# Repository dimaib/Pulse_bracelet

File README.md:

# Oxemetry and pulsometry
## Description
This system allows you to distribute people between warehouse equipment and give permission to control certain types of machines. It also allows you to take into account the working hours of employees and conduct convenient analytics according to these hours.
## System Composition
- Wrist bracelet
	>The printed circuit board and circuit diagram of the device are created in [KiCad](https://www.kicad.org) 
	Firmware created in Keil uVision for ARM in C languages
- Server that receives data from devices and adds this data to the database
	>The server part was created in Visual Studio C ++, as a console application
	MySQL was used as the database. And MySQL Workbench for administration

## Main view PCB

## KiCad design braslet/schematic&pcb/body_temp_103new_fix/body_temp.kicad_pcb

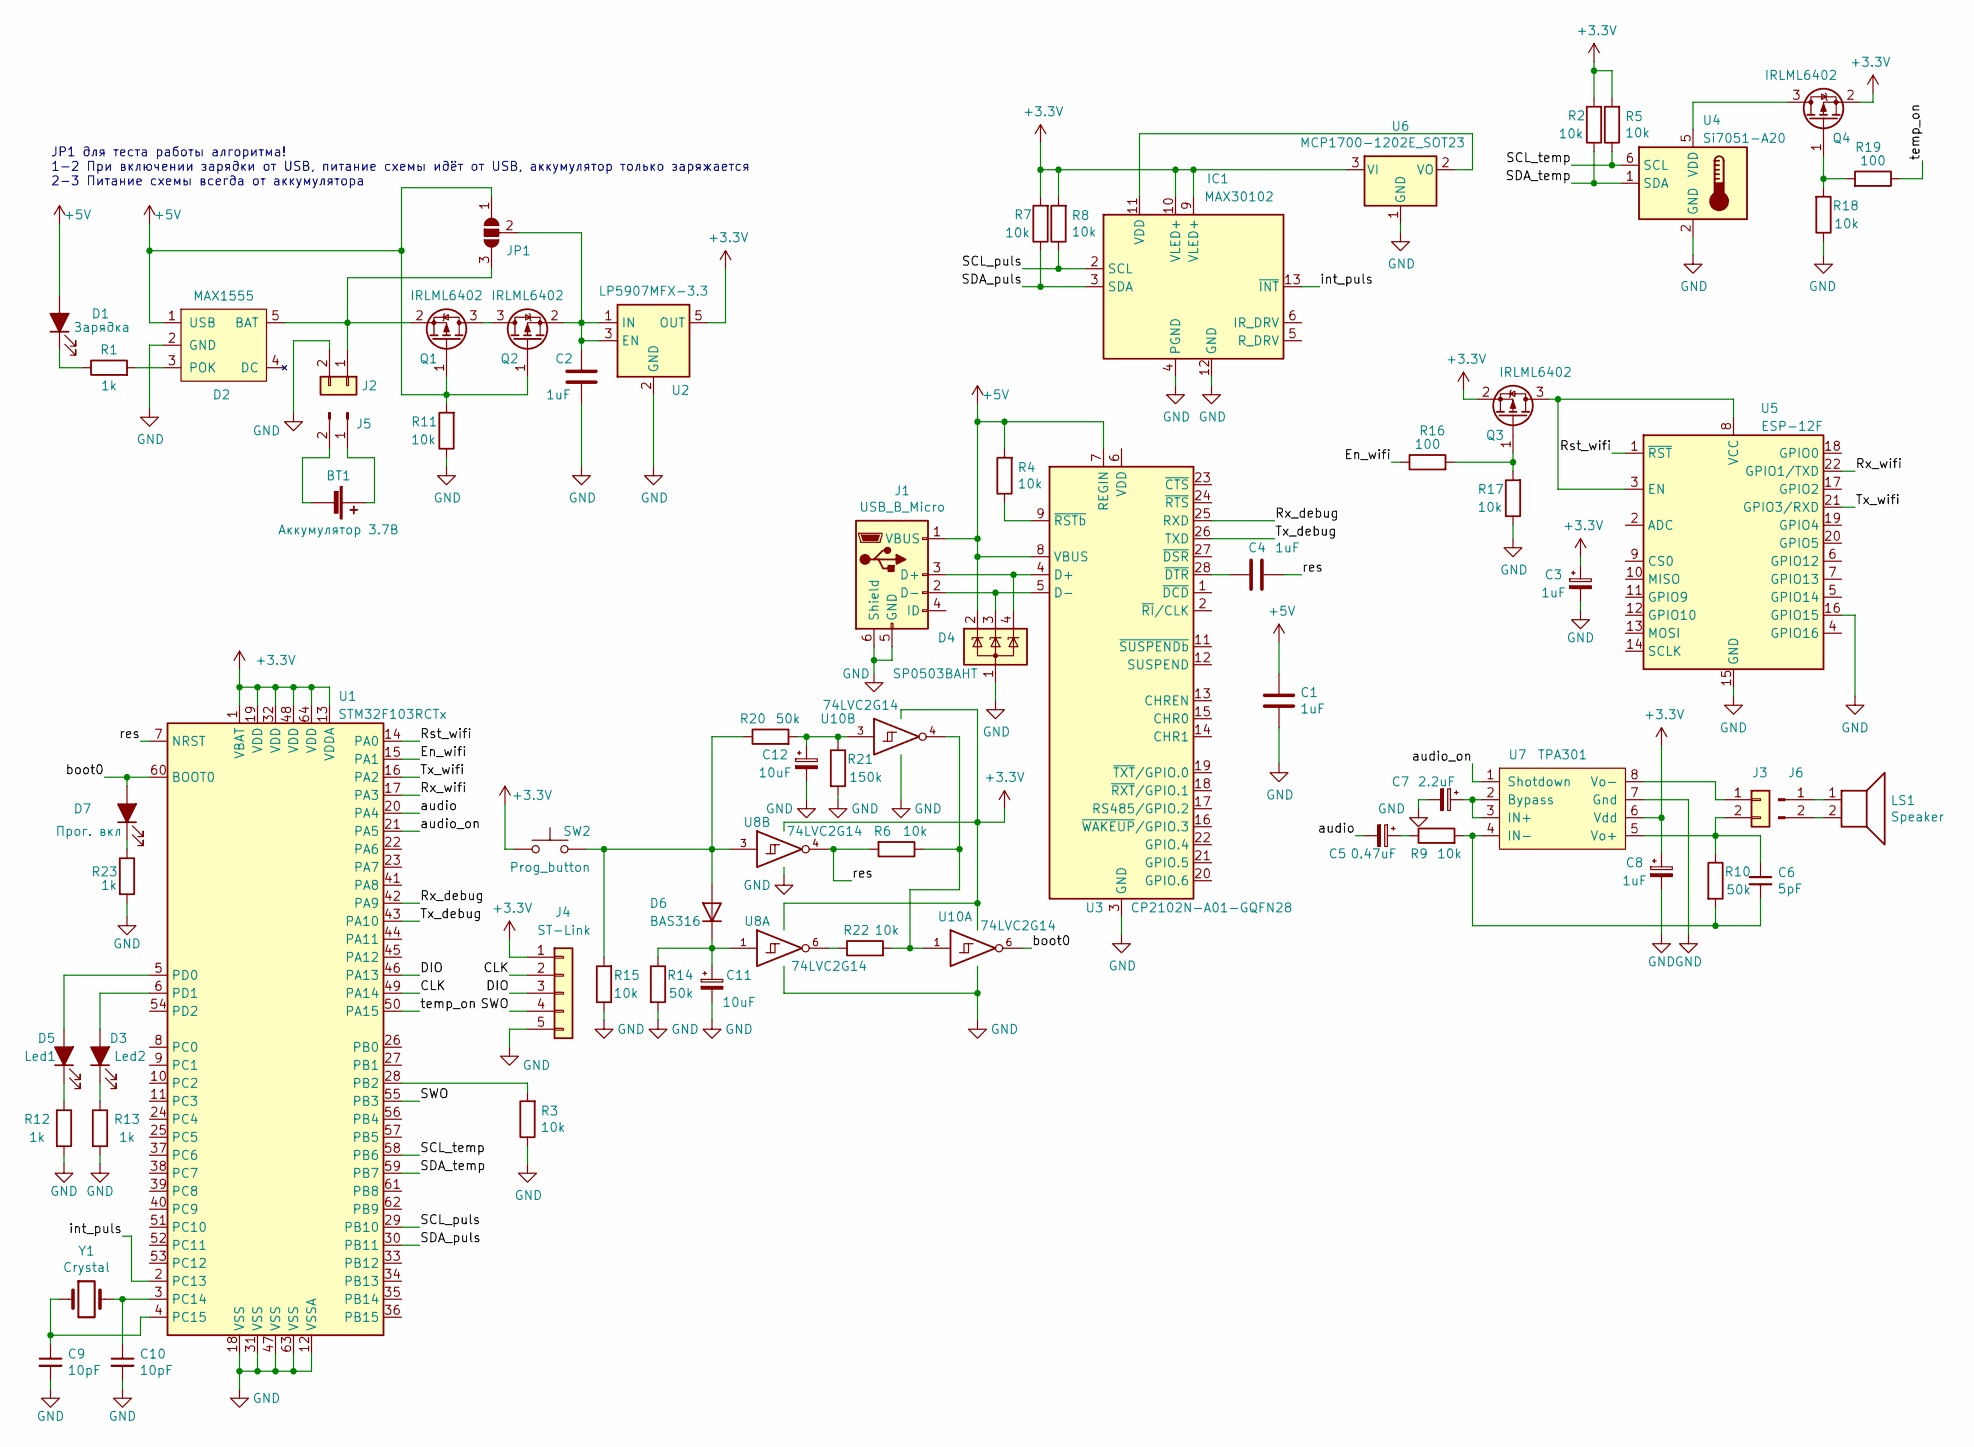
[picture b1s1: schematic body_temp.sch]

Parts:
BT1: Аккумулятор 3.7В
C1, C2, C4: 1uF; C_0603_1608Metric
C3, C8: 1uF; CP_EIA-3216-18_Kemet-A
C5: 0.47uF; CP_EIA-3216-18_Kemet-A
C6: 5pF; C_0603_1608Metric
C7: 2.2uF; CP_EIA-3216-18_Kemet-A
C9, C10: 10pF; C_0603_1608Metric
C11, C12: 10uF; CP_EIA-3216-18_Kemet-A
D1: Зарядка; LED_0603_1608Metric
D2: MAX1555; SOT-23-5
D3: Led2; LED_0603_1608Metric
D4: SP0503BAHT; SOT-143
D5: Led1; LED_0603_1608Metric
D6: BAS316; D_SOD-323
D7: Прог. вкл; LED_0603_1608Metric
IC1: MAX30102; Maxim_OLGA-14_3.3x5.6mm_P0.8mm
J1: USB_B_Micro; USB_Micro-B_Molex-105017-0001
J2: Аккумулятор на плату; ZH_Conn_02x01
J3: Динамик на плату; ZH_Conn_02x01
J4: ST-Link; ds1066-05m_2.0mm
J5: Аккумулятор на кабель
J6: Динамик на кабель
JP1: SolderJumper_3_Open; SolderJumper-3_P1.3mm_Open_RoundedPad1.0x1.5mm
LS1: Speaker
Q1, Q2, Q3, Q4: IRLML6402; SOT-23
R1, R12, R13, R23: 1k; R_0603_1608Metric
R2, R3, R4, R5, R6, R7, R8, R9, R11, R15, R17, R18, R22: 10k; R_0603_1608Metric
R10, R14, R20: 50k; R_0603_1608Metric
R16, R19: 100; R_0603_1608Metric
R21: 150k; R_0603_1608Metric
SW2: Prog_button; SW_SPST_EVQP7C
U1: STM32F103RCTx; LQFP-64_10x10mm_P0.5mm
U2: LP5907MFX-3.3; SOT-23-5
U3: CP2102N-A01-GQFN28; QFN-28-1EP_5x5mm_P0.5mm_EP3.35x3.35mm
U4: Si7051-A20; DFN-6-1EP_3x3mm_P1mm_EP1.5x2.4mm
U5: ESP-12F; ESP-12E
U6: MCP1700-1202E_SOT23; SOT-23
U7: TPA301; MSOP-8-1EP_3x3mm_P0.65mm_EP1.95x2.15mm
U8, U10: 74LVC2G14; SOT-23-6
Y1: Crystal; Crystal_SMD_G8-2Pin_3.2x1.5mm

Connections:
+3V3: C3.1, C8.1, IC1.9 (VLED+), IC1.10 (VLED+), J4.1, Q3.2 (S), Q4.2 (S), R2.2, R5.2, R7.2, R8.2, SW2.1, U1.1 (VBAT), U1.13 (VDDA), U1.19 (VDD), U1.32 (VDD), U1.48 (VDD), U1.64 (VDD), U2.5 (OUT), U6.3 (VI), U7.6 (Vdd), U8.5 (VCC), U10.5 (VCC)
+5V: C1.1, D1.2 (A), D2.1 (USB), D4.2 (K), J1.1 (VBUS), JP1.1 (A), Q1.1 (G), Q2.1 (G), R4.2, R11.2, U3.7 (REGIN), U3.8 (VBUS)
/CLK: J4.2, U1.49 (PA14)
/DIO: J4.3, U1.46 (PA13)
/En_wifi: R16.1, U1.15 (PA1)
/Rst_wifi: U1.14 (PA0), U5.1 (~RST)
/Rx_debug: U1.42 (PA9), U3.25 (RXD)
/Rx_wifi: U1.17 (PA3), U5.22 (GPIO1/TXD)
/SCL_puls: IC1.2 (SCL), R8.1, U1.29 (PB10)
/SCL_temp: R5.1, U1.58 (PB6), U4.6 (SCL)
/SDA_puls: IC1.3 (SDA), R7.1, U1.30 (PB11)
/SDA_temp: R2.1, U1.59 (PB7), U4.1 (SDA)
/SWO: J4.4, U1.55 (PB3)
/Tx_debug: U1.43 (PA10), U3.26 (TXD)
/Tx_wifi: U1.16 (PA2), U5.21 (GPIO3/RXD)
/audio: C5.2, U1.20 (PA4)
/audio_on: U1.21 (PA5), U7.1 (Shotdown)
/boot0: D7.2 (A), U1.60 (BOOT0), U10.6
/int_puls: IC1.13 (~INT), U1.2 (PC13)
/res: C4.1, R6.2, U1.7 (NRST), U8.4
/temp_on: R19.1, U1.50 (PA15)
GND: C1.2, C2.2, C3.2, C7.2, C8.2, C9.2, C10.2, C11.2, C12.2, D2.2 (GND), D4.1 (A), IC1.4 (PGND), IC1.12 (GND), J1.5 (GND), J1.6 (Shield), J2.2, J4.5, R3.1, R11.1, R12.2, R13.2, R14.2, R15.1, R17.1, R18.1, R21.2, R23.2, U1.12 (VSSA), U1.18 (VSS), U1.31 (VSS), U1.47 (VSS), U1.63 (VSS), U2.2 (GND), U3.3 (GND), U3.29 (GND), U4.2 (GND), U5.15 (GND), U5.16 (GPIO15), U6.1 (GND), U7.7 (Gnd), U8.2 (GND), U10.2 (GND)
unnamed: BT1.1 (+), J5.1
unnamed: BT1.2 (-), J5.2
unnamed: C2.1, JP1.2 (C), Q2.2 (S), U2.1 (IN), U2.3 (EN)
unnamed: C4.2, U3.28 (~DTR)
unnamed: C5.1, R9.1
unnamed: C6.1, J3.2, R10.1, U7.5 (Vo+)
unnamed: C6.2, R9.2, R10.2, U7.4 (IN-)
unnamed: C7.1, U7.2 (Bypass), U7.3 (IN+)
unnamed: C9.1, U1.4 (PC15), Y1.1
unnamed: C10.1, U1.3 (PC14), Y1.2
unnamed: C11.1, D6.1 (K), R14.1, U8.1
unnamed: C12.1, R20.2, R21.1, U10.3
unnamed: D1.1 (K), R1.1
unnamed: D2.3 (POK), R1.2
unnamed: D2.5 (BAT), J2.1, JP1.3 (B), Q1.2 (S)
unnamed: D3.1 (K), R13.1
unnamed: D3.2 (A), U1.6 (PD1)
unnamed: D4.3 (K), J1.2 (D-), U3.5 (D-)
unnamed: D4.4 (K), J1.3 (D+), U3.4 (D+)
unnamed: D5.1 (K), R12.1
unnamed: D5.2 (A), U1.5 (PD0)
unnamed: D6.2 (A), R15.2, R20.1, SW2.2, U8.3
unnamed: D7.1 (K), R23.1
unnamed: IC1.11 (VDD), U6.2 (VO)
unnamed: J3.1, U7.8 (Vo-)
unnamed: J6.1, LS1.1
unnamed: J6.2, LS1.2
unnamed: Q1.3 (D), Q2.3 (D)
unnamed: Q3.1 (G), R16.2, R17.2
unnamed: Q3.3 (D), U5.3 (EN), U5.8 (VCC)
unnamed: Q4.1 (G), R18.2, R19.2
unnamed: Q4.3 (D), U4.5 (VDD)
unnamed: R3.2, U1.28 (PB2)
unnamed: R4.1, U3.9 (~RSTb)
unnamed: R22.1, U8.6
unnamed: R6.1, R22.2, U10.1, U10.4

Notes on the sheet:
JP1 для теста работы алгоритма! 1-2 При включении зарядки от USB, питание схемы идёт от USB, аккумулятор только заряжается 2-3 Питание схемы всегда от аккумулятора

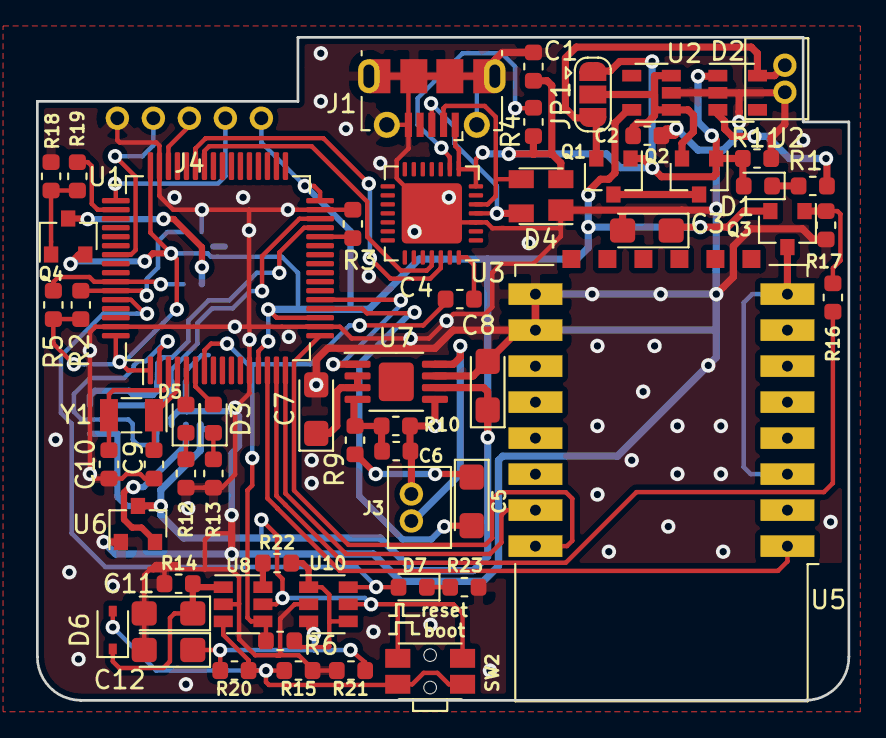
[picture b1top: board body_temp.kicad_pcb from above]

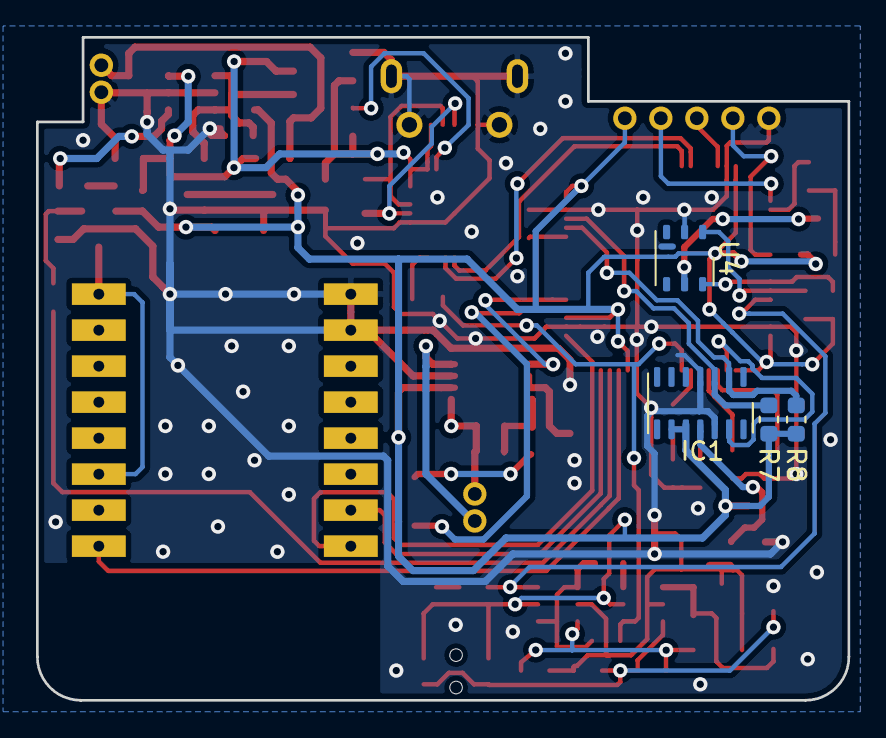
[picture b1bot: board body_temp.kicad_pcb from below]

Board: 2 copper layers, 45.1 x 36.8 mm, 63 parts (4 on the bottom side), 54 nets.

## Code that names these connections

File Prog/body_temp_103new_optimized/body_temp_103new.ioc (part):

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Mcu.Name=STM32F103R(C-D-E)Tx
Mcu.Package=LQFP64
Mcu.UserName=STM32F103RCTx
PA0-WKUP.GPIOParameters=GPIO_Label
PA0-WKUP.GPIO_Label=rst_wifi
PA0-WKUP.Signal=GPIO_Output
PA1.GPIOParameters=GPIO_Label
PA1.GPIO_Label=en_wifi
PA1.Signal=GPIO_Output
PA10.GPIOParameters=GPIO_Label
PA10.GPIO_Label=rx1_debug
PA10.Mode=Asynchronous
PA10.Signal=USART1_RX
PA13.Mode=Trace_Asynchronous_SW
PA13.Signal=SYS_JTMS-SWDIO
PA14.Mode=Trace_Asynchronous_SW
PA14.Signal=SYS_JTCK-SWCLK
PA2.GPIOParameters=GPIO_Label
PA2.GPIO_Label=tx2_wifi
PA2.Mode=Asynchronous
PA2.Signal=USART2_TX
PA3.GPIOParameters=GPIO_Label
PA3.GPIO_Label=rx2_wifi
PA3.Mode=Asynchronous
PA3.Signal=USART2_RX
PA4.GPIOParameters=GPIO_Label
PA4.GPIO_Label=audio
PA4.Signal=COMP_DAC1_group
PA5.GPIOParameters=GPIO_Label
PA5.GPIO_Label=audio_on
PA5.Signal=GPIO_Output
PA9.GPIOParameters=GPIO_Label
PA9.GPIO_Label=tx1_debug
PA9.Mode=Asynchronous
PA9.Signal=USART1_TX
PB10.Mode=I2C
PB10.Signal=I2C2_SCL
PB11.Mode=I2C
PB11.Signal=I2C2_SDA
PB3.Mode=Trace_Asynchronous_SW
PB3.Signal=SYS_JTDO-TRACESWO
PB6.Mode=I2C
PB6.Signal=I2C1_SCL
PB7.Mode=I2C
PB7.Signal=I2C1_SDA
PC13-TAMPER-RTC.GPIOParameters=GPIO_PuPd,GPIO_Label
PC13-TAMPER-RTC.GPIO_Label=int_puls
PC13-TAMPER-RTC.GPIO_PuPd=GPIO_NOPULL
PC13-TAMPER-RTC.Signal=GPIO_Input
PD0-OSC_IN.GPIOParameters=GPIO_Label
PD0-OSC_IN.GPIO_Label=led1
PD0-OSC_IN.Signal=GPIO_Output
PD1-OSC_OUT.GPIOParameters=GPIO_Label
PD1-OSC_OUT.GPIO_Label=led2
PD1-OSC_OUT.Signal=GPIO_Output
RCC.SYSCLKFreq_VALUE=64000000
RCC.SYSCLKSource=RCC_SYSCLKSOURCE_PLLCLK
board=custom

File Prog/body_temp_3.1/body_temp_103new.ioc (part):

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Mcu.Name=STM32F103R(C-D-E)Tx
Mcu.Package=LQFP64
Mcu.UserName=STM32F103RCTx
PA1.GPIOParameters=GPIO_Label
PA1.GPIO_Label=rst_wifi
PA1.Signal=GPIO_Output
PA10.GPIOParameters=GPIO_Label
PA10.GPIO_Label=rx1_debug
PA10.Mode=Asynchronous
PA10.Signal=USART1_RX
PA13.Mode=Trace_Asynchronous_SW
PA13.Signal=SYS_JTMS-SWDIO
PA14.Mode=Trace_Asynchronous_SW
PA14.Signal=SYS_JTCK-SWCLK
PA2.GPIOParameters=GPIO_Label
PA2.GPIO_Label=tx2_wifi
PA2.Mode=Asynchronous
PA2.Signal=USART2_TX
PA3.GPIOParameters=GPIO_Label
PA3.GPIO_Label=rx2_wifi
PA3.Mode=Asynchronous
PA3.Signal=USART2_RX
PA4.GPIOParameters=GPIO_Label
PA4.GPIO_Label=audio
PA4.Signal=COMP_DAC1_group
PA5.GPIOParameters=GPIO_Label
PA5.GPIO_Label=audio_on
PA5.Signal=GPIO_Output
PA6.GPIOParameters=GPIO_Label
PA6.GPIO_Label=Wifi_on
PA6.Signal=GPIO_Output
PA7.GPIOParameters=GPIO_Label
PA7.GPIO_Label=Ubat_ADC7
PA7.Signal=ADCx_IN7
PA9.GPIOParameters=GPIO_Label
PA9.GPIO_Label=tx1_debug
PA9.Mode=Asynchronous
PA9.Signal=USART1_TX
PB10.GPIOParameters=GPIO_Label
PB10.GPIO_Label=SCL_puls_accel
PB10.Mode=I2C
PB10.Signal=I2C2_SCL
PB11.GPIOParameters=GPIO_Label
PB11.GPIO_Label=SDA_puls_accel
PB11.Mode=I2C
PB11.Signal=I2C2_SDA
PB12.GPIOParameters=GPIO_Label
PB12.GPIO_Label=int_puls
PB12.Signal=GPIO_Input
PB13.GPIOParameters=GPIO_Label
PB13.GPIO_Label=pulse_on
PB13.Signal=GPIO_Output
PB14.GPIOParameters=GPIO_Label
PB14.GPIO_Label=int_accel
PB14.Signal=GPIO_Input
PB15.GPIOParameters=GPIO_Label
PB15.GPIO_Label=ext_button
PB15.Signal=GPIO_Input
PB3.Mode=Trace_Asynchronous_SW
PB3.Signal=SYS_JTDO-TRACESWO
PB6.GPIOParameters=GPIO_Label
PB6.GPIO_Label=SCL_temp
PB6.Mode=I2C
PB6.Signal=I2C1_SCL
PB7.GPIOParameters=GPIO_Label
PB7.GPIO_Label=SDA_temp
PB7.Mode=I2C
PB7.Signal=I2C1_SDA
PC3.GPIOParameters=GPIO_Label
PC3.GPIO_Label=temp_on
PC3.Signal=GPIO_Output
PD0-OSC_IN.GPIOParameters=GPIO_Label
PD0-OSC_IN.GPIO_Label=led1
PD0-OSC_IN.Signal=GPIO_Output
RCC.SYSCLKFreq_VALUE=64000000
RCC.SYSCLKSource=RCC_SYSCLKSOURCE_PLLCLK
board=custom

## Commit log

2022-04-23 add readme
2022-04-23 add screen
2022-04-23 Update README.md
    edit readme
